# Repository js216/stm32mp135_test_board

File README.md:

# Test board using STM32MP135

A minimum working example of STM32MP135-based board, breaking out almost all the
pins.

### PCB layout

Find the KiCad files under `kicad/`. This includes the BOM and position files as
used to fabricate the board with JLCPCB. For quick reference, check out the
[`schematics.pdf`](https://github.com/js216/stm32mp135_test_board/blob/81400d63cfe211af686742da545c3347b2757c94/kicad/schematics.pdf).

### CubeMX files

The pin assignment was done using STM32CubeMX. Reluctantly, since it's one of
those bloated modern programs that manage to run slowly even on the fastest
computers available. But it does generate a nice overview of the pin assignment.

### Bare-metal projects

Under `baremetal` you can find a sequence of simple projects for getting started
with debugging this board. (See also the debugging walkthrough in
[this](https://embd.cc/linux-bringup-on-custom-stm32mp135-board) blog post.) The
projects are as follows:

- `blink` will blink the red LED on the board, thus proving that the chip works
  and that we have a way to program it (namely the `uart_boot.py` script,
  described in more details
  [here](https://embd.cc/boot-stm32mp135-over-uart-with-python)).

- `ddr_test`: Initialize DDR3L memory, fill it with pseudorandom bits, and
  confirm that reading from the memory returns the same bit sequence.

- `STM32DDRFW-UTIL`: A simplified version of the
  [tool](https://github.com/STMicroelectronics/STM32DDRFW-UTIL) provided by ST.

- `sd_test`: Initialize SD card, and read out the first few bytes.

- `usb_test`: Checks that data can be loaded from the USB interface (enumerated
  as a "flash drive") to the DDR memory.

- `qspi`: QUADSPI bring-up app.  Initialises the peripheral at ~1 MHz, then
  loops issuing JEDEC-ID reads (`0x9F` + 3 bytes) so the bus can be verified
  on a scope or logic analyser.  Designed for exercising QSPI wiring against
  a user-supplied FPGA slave.  The QUADSPI peripheral is poked via raw
  registers; HAL is used only for GPIO pin-mux, RCC clock muxing, and UART
  output.

All projects are completely independent of each other, and each directory
contains all drivers and other files needed to build the firmware image by just
calling `make`. This means that some of the source files are duplicated; so be
it! BSP packages are in my opinion too "integrated", where everything depends on
everything else. There are occasions---such as this one---where making a copy of
a couple files is the simplest and correct thing to do.

### Building a Linux system

The following directories contain the files needed to build a complete Linux
system image, ready for flashing to the board:

- `bootloader`: USB MSC Bootloader for STM32MP135
  [(link)](https://github.com/js216/stm32mp135-bootloader)
- `linux`: clone of the ST-modified kernel fork
  [(link)](https://github.com/STMicroelectronics/linux)
- `dtbs`: board-specific device tree sources

To build the project, run `make patch all` and watch the SD card image appear
under `build/`. More explanation can be found in
[this](https://embd.cc/build-linux-for-stm32mp135-in-under-50-lines-of-makefile)
blog post, or in the bootloader
[Readme](https://github.com/js216/stm32mp135-bootloader).

*Note:* The
["meta-Makefile"](https://github.com/js216/stm32mp135_test_board/blob/main/Makefile)
for this project is somewhat unusual: it does not track dependencies and its
recipes are fragile, so configuration changes may require editing the recipes
directly. Its purpose is not to provide a robust build system, but to serve as a
shortcut for repetitive command sequences. Being only about 50 lines, modifying
it directly is simpler than learning a separate configuration language. Treat it
as a minimal, linear workflow script wrapped in Make syntax rather than a
conventional build system.

### References

- [Ethernet on Bare-Metal STM32MP13](https://embd.cc/ethernet-on-baremetal-stm32mp135)
- [LCD/CTP on Bare-Metal STM32MP135](https://embd.cc/lcd-ctp-on-baremetal-stm32mp135)
- [Debugging STM32MP135 Kernel Decompression](https://embd.cc/debugging-stm32mp135-kernel-decompression)
- [Build Linux for STM32MP135 in under 50 Lines of Makefile](https://embd.cc/build-linux-for-stm32mp135-in-under-50-lines-of-makefile)
- [SD card on bare-metal STM32MP135](https://embd.cc/sdcard-on-bare-metal-stm32mp135)
- [Unsecuring STM32MP135 TrustZone](https://embd.cc/unsecuring-stm32mp135-trustzone)
- [Linux Bring-Up on a Custom STM32MP135 Board](https://embd.cc/linux-bringup-on-custom-stm32mp135-board)
- [USB Bring-Up on a Custom STM32MP135 Board](https://embd.cc/usb-bringup-on-custom-stm32mp135-board)
- [STM32MP135 Flashing via USB with STM32CubeProg](https://embd.cc/stm32mp135-linux-cubeprog)
- [Boot STM32MP135 Over UART With Python](https://embd.cc/boot-stm32mp135-over-uart-with-python)
- [Buildroot files for a similar project](https://github.com/js216/stm32mp135_simple/tree/main)

### Author

Jakob Kastelic, Stanford Research Systems

NOTE: PORTIONS OF THIS REPOSITORY CONTAIN SOURCE CODE COPYRIGHTED BY
STMICROELECTRONICS. SUCH FILES ARE PROVIDED UNDER STMICROELECTRONICS' ORIGINAL
LICENSE TERMS, WHICH ARE INCLUDED WITH THOSE FILES. NO RIGHTS ARE GRANTED BEYOND
THOSE TERMS. THIS REPOSITORY MAY NOT BE USED WITH NON-ST HARDWARE UNLESS
PERMITTED BY ST'S LICENSE. ALL PROPRIETARY NOTICES MUST REMAIN INTACT.

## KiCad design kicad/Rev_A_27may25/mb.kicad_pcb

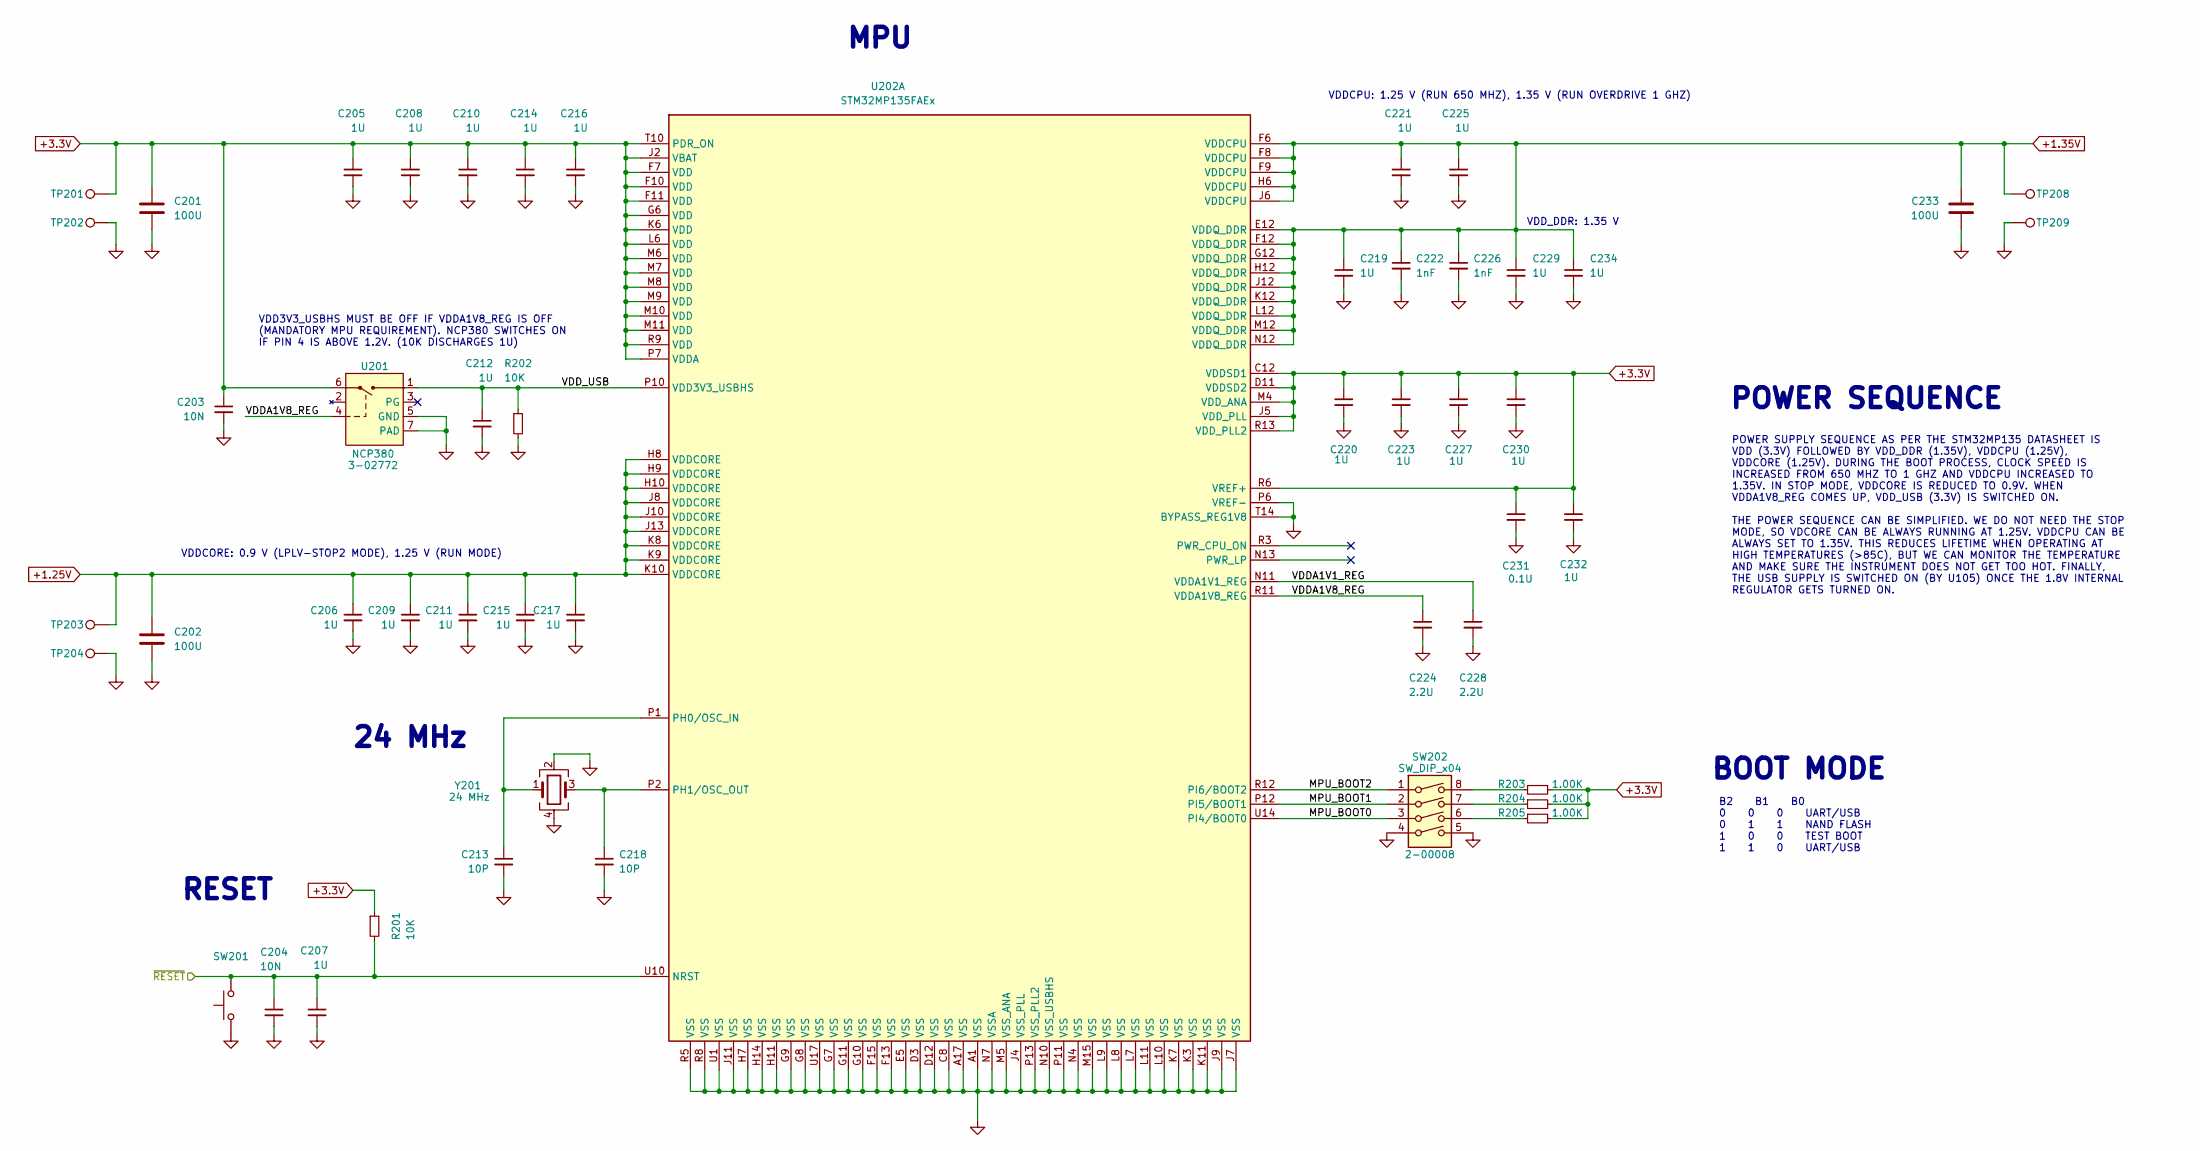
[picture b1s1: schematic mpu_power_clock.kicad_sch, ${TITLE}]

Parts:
C201, C202, C233: 100U; C_1206_3216Metric; JLCPCB C15008
C203, C204: 10N; C_0402_1005Metric; JLCPCB C15195
C205, C206, C207, C208, C209, C210, C211, C212, C214, C215, C216, C217, C219, C220, C221, C223, C225, C227, C229, C230, C232, C234: 1U; C_0402_1005Metric; JLCPCB C52923
C213, C218: 10P; C_0402_1005Metric; JLCPCB C32949
C222, C226: 1nF; C_0402_1005Metric; JLCPCB C1523
C224, C228: 2.2U; C_0402_1005Metric; JLCPCB C12530
C231: 0.1U; C_0402_1005Metric; JLCPCB C307331
R201, R202: 10K; R_0402_1005Metric; JLCPCB C25744
R203, R204, R205: 1.00K; R_0402_1005Metric; JLCPCB C11702
SW201: Omron B3F-1052; SW_TH_Tactile_Omron_B3F-10xx
SW202: SW_DIP_x04; SW_DIP_SPSTx04_Slide_9.78x12.34mm_W7.62mm_P2.54mm
TP201, TP203, TP208: Keystone 5005 (red); TestPoint_Keystone_5005-5009_Compact
TP202, TP204, TP209: Keystone 5006 (black); TestPoint_Keystone_5005-5009_Compact
U201: NCP380; DFN-6-1EP_2x2mm_P0.65mm_EP1x1.6mm; JLCPCB C145185
U202: STM32MP135FAEx; LFBGA-289_14x14mm_Layout17x17_P0.8mm; JLCPCB C7501745
Y201: 24 MHz; Crystal_SMD_3225-4Pin_3.2x2.5mm; MPN YXC Crystal Oscillators X322524MRB4SI; JLCPCB C70571

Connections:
+1.25V: C202.1, C206.1, C209.1, C211.1, C215.1, C217.1, TP203.1, U202.H8 (VDDCORE), U202.H9 (VDDCORE), U202.H10 (VDDCORE), U202.J8 (VDDCORE), U202.J10 (VDDCORE), U202.J13 (VDDCORE), U202.K8 (VDDCORE), U202.K9 (VDDCORE), U202.K10 (VDDCORE)
+1.35V: C219.1, C221.1, C222.1, C225.1, C226.1, C229.1, C233.1, C234.1, TP208.1, U202.E12 (VDDQ_DDR), U202.F6 (VDDCPU), U202.F8 (VDDCPU), U202.F9 (VDDCPU), U202.F12 (VDDQ_DDR), U202.G12 (VDDQ_DDR), U202.H6 (VDDCPU), U202.H12 (VDDQ_DDR), U202.J6 (VDDCPU), U202.J12 (VDDQ_DDR), U202.K12 (VDDQ_DDR), U202.L12 (VDDQ_DDR), U202.M12 (VDDQ_DDR), U202.N12 (VDDQ_DDR); also elsewhere on the board
+3.3V: C201.1, C203.1, C205.1, C208.1, C210.1, C214.1, C216.1, C220.1, C223.1, C227.1, C230.1, C231.1, C232.1, R201.1, R203.2, R204.2, R205.2, TP201.1, U201.6, U202.C12 (VDDSD1), U202.D11 (VDDSD2), U202.F7 (VDD), U202.F10 (VDD), U202.F11 (VDD), U202.G6 (VDD), U202.J2 (VBAT), U202.J5 (VDD_PLL), U202.K6 (VDD), U202.L6 (VDD), U202.M4 (VDD_ANA), U202.M6 (VDD), U202.M7 (VDD), U202.M8 (VDD), U202.M9 (VDD), U202.M10 (VDD), U202.M11 (VDD), U202.P7 (VDDA), U202.R6 (VREF+), U202.R9 (VDD), U202.R13 (VDD_PLL2), U202.T10 (PDR_ON); also elsewhere on the board
/MPU Power & Clock/MPU_BOOT0: SW202.3, U202.U14 (PI4/BOOT0)
/MPU Power & Clock/MPU_BOOT1: SW202.2, U202.P12 (PI5/BOOT1)
/MPU Power & Clock/MPU_BOOT2: SW202.1, U202.R12 (PI6/BOOT2)
/MPU Power & Clock/VDDA1V1_REG: C228.1, U202.N11 (VDDA1V1_REG)
/MPU Power & Clock/VDDA1V8_REG: C224.1, U201.4, U202.R11 (VDDA1V8_REG)
/MPU Power & Clock/VDD_USB: C212.1, R202.1, U201.1, U202.P10 (VDD3V3_USBHS)
/~RESET: C204.1, C207.1, R201.2, SW201.2, U202.U10 (NRST); also elsewhere on the board
GND: C201.2, C202.2, C203.2, C204.2, C205.2, C206.2, C207.2, C208.2, C209.2, C210.2, C211.2, C212.2, C213.2, C214.2, C215.2, C216.2, C217.2, C218.2, C219.2, C220.2, C221.2, C222.2, C223.2, C224.2, C225.2, C226.2, C227.2, C228.2, C229.2, C230.2, C231.2, C232.2, C233.2, C234.2, R202.2, SW201.1, SW202.4, SW202.5, TP202.1, TP204.1, TP209.1, U201.5 (GND), U201.7 (PAD), U202.A1 (VSS), U202.A17 (VSS), U202.C8 (VSS), U202.D3 (VSS), U202.D12 (VSS), U202.E5 (VSS), U202.F13 (VSS), U202.F15 (VSS), U202.G7 (VSS), U202.G8 (VSS), U202.G9 (VSS), U202.G10 (VSS), U202.G11 (VSS), U202.H7 (VSS), U202.H11 (VSS), U202.H14 (VSS), U202.J4 (VSS_PLL), U202.J7 (VSS), U202.J9 (VSS), U202.J11 (VSS), U202.K3 (VSS), U202.K7 (VSS), U202.K11 (VSS), U202.L7 (VSS), U202.L8 (VSS), U202.L9 (VSS), U202.L10 (VSS), U202.L11 (VSS), U202.M5 (VSS_ANA), U202.M15 (VSS), U202.N4 (VSS), U202.N7 (VSSA), U202.N10 (VSS_USBHS), U202.P6 (VREF-), U202.P11 (VSS), U202.P13 (VSS_PLL2), U202.R5 (VSS), U202.R8 (VSS), U202.T14 (BYPASS_REG1V8), U202.U1 (VSS), U202.U17 (VSS), Y201.2, Y201.4; also elsewhere on the board
unnamed: R203.1, SW202.8
unnamed: R204.1, SW202.7
unnamed: R205.1, SW202.6
unnamed: C213.1, U202.P1 (PH0/OSC_IN), Y201.1
unnamed: C218.1, U202.P2 (PH1/OSC_OUT), Y201.3

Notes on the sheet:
B2 B1 B0 0 0 0 UART/USB 0 1 1 NAND FLASH 1 0 0 TEST BOOT 1 1 0 UART/USB
VDDCPU: 1.25 V (RUN 650 MHZ), 1.35 V (RUN OVERDRIVE 1 GHZ)
MPU
BOOT MODE
POWER SUPPLY SEQUENCE AS PER THE STM32MP135 DATASHEET IS VDD (3.3V) FOLLOWED BY VDD_DDR (1.35V), VDDCPU (1.25V), VDDCORE (1.25V). DURING THE BOOT PROCESS, CLOCK SPEED IS INCREASED FROM 650 MHZ TO 1 GHZ AND VDDCPU INCREASED TO 1.35V. IN STOP MODE, VDDCORE IS REDUCED TO 0.9V. WHEN VDDA1V8_REG COMES U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
POWER SEQUENCE
VDD3V3_USBHS MUST BE OFF IF VDDA1V8_REG IS OFF (MANDATORY MPU REQUIREMENT). NCP380 SWITCHES ON IF PIN 4 IS ABOVE 1.2V. (10K DISCHARGES 1U)
VDD_DDR: 1.35 V
24 MHz
VDDCORE: 0.9 V (LPLV-STOP2 MODE), 1.25 V (RUN MODE)
RESET

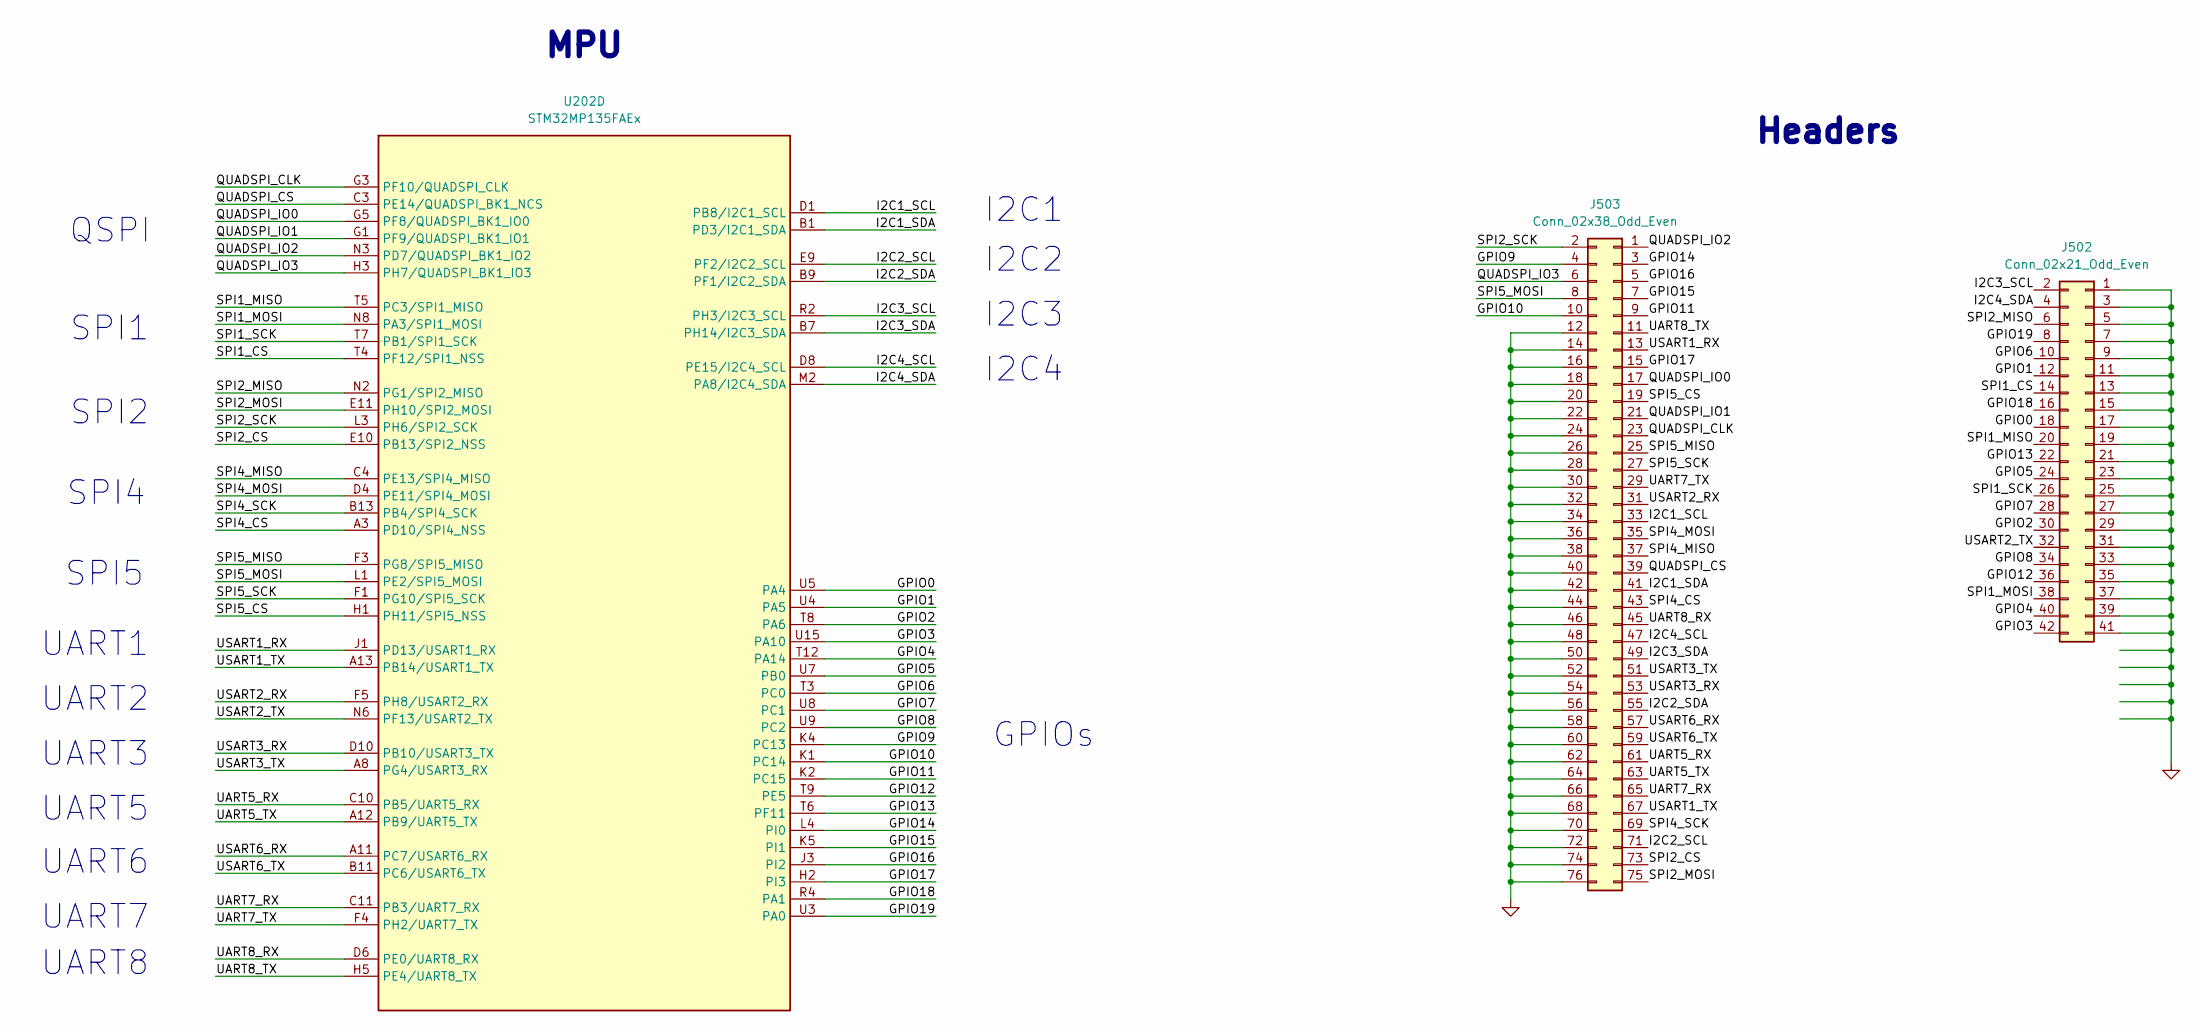
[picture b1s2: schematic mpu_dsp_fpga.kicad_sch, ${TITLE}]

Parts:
J502: Conn_02x21_Odd_Even; PinHeader_2x21_P2.54mm_Vertical
J503: Conn_02x38_Odd_Even; PinHeader_2x38_P2.54mm_Vertical
U202: STM32MP135FAEx; LFBGA-289_14x14mm_Layout17x17_P0.8mm; JLCPCB C7501745

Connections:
/MPU Extra Pins/GPIO0: J502.18, U202.U5 (PA4)
/MPU Extra Pins/GPIO1: J502.12, U202.U4 (PA5)
/MPU Extra Pins/GPIO2: J502.30, U202.T8 (PA6)
/MPU Extra Pins/GPIO3: J502.42, U202.U15 (PA10)
/MPU Extra Pins/GPIO4: J502.40, U202.T12 (PA14)
/MPU Extra Pins/GPIO5: J502.24, U202.U7 (PB0)
/MPU Extra Pins/GPIO6: J502.10, U202.T3 (PC0)
/MPU Extra Pins/GPIO7: J502.28, U202.U8 (PC1)
/MPU Extra Pins/GPIO8: J502.34, U202.U9 (PC2)
/MPU Extra Pins/GPIO9: J503.4, U202.K4 (PC13)
/MPU Extra Pins/GPIO10: J503.10, U202.K1 (PC14)
/MPU Extra Pins/GPIO11: J503.9, U202.K2 (PC15)
/MPU Extra Pins/GPIO12: J502.36, U202.T9 (PE5)
/MPU Extra Pins/GPIO13: J502.22, U202.T6 (PF11)
/MPU Extra Pins/GPIO14: J503.3, U202.L4 (PI0)
/MPU Extra Pins/GPIO15: J503.7, U202.K5 (PI1)
/MPU Extra Pins/GPIO16: J503.5, U202.J3 (PI2)
/MPU Extra Pins/GPIO17: J503.15, U202.H2 (PI3)
/MPU Extra Pins/GPIO18: J502.16, U202.R4 (PA1)
/MPU Extra Pins/GPIO19: J502.8, U202.U3 (PA0)
/MPU Extra Pins/I2C1_SCL: J503.33, U202.D1 (PB8/I2C1_SCL)
/MPU Extra Pins/I2C1_SDA: J503.41, U202.B1 (PD3/I2C1_SDA)
/MPU Extra Pins/I2C2_SCL: J503.71, U202.E9 (PF2/I2C2_SCL)
/MPU Extra Pins/I2C2_SDA: J503.55, U202.B9 (PF1/I2C2_SDA)
/MPU Extra Pins/I2C3_SCL: J502.2, U202.R2 (PH3/I2C3_SCL)
/MPU Extra Pins/I2C3_SDA: J503.49, U202.B7 (PH14/I2C3_SDA)
/MPU Extra Pins/I2C4_SCL: J503.47, U202.D8 (PE15/I2C4_SCL)
/MPU Extra Pins/I2C4_SDA: J502.4, U202.M2 (PA8/I2C4_SDA)
/MPU Extra Pins/QUADSPI_CLK: J503.23, U202.G3 (PF10/QUADSPI_CLK)
/MPU Extra Pins/QUADSPI_CS: J503.39, U202.C3 (PE14/QUADSPI_BK1_NCS)
/MPU Extra Pins/QUADSPI_IO0: J503.17, U202.G5 (PF8/QUADSPI_BK1_IO0)
/MPU Extra Pins/QUADSPI_IO1: J503.21, U202.G1 (PF9/QUADSPI_BK1_IO1)
/MPU Extra Pins/QUADSPI_IO2: J503.1, U202.N3 (PD7/QUADSPI_BK1_IO2)
/MPU Extra Pins/QUADSPI_IO3: J503.6, U202.H3 (PH7/QUADSPI_BK1_IO3)
/MPU Extra Pins/SPI1_CS: J502.14, U202.T4 (PF12/SPI1_NSS)
/MPU Extra Pins/SPI1_MISO: J502.20, U202.T5 (PC3/SPI1_MISO)
/MPU Extra Pins/SPI1_MOSI: J502.38, U202.N8 (PA3/SPI1_MOSI)
/MPU Extra Pins/SPI1_SCK: J502.26, U202.T7 (PB1/SPI1_SCK)
/MPU Extra Pins/SPI2_CS: J503.73, U202.E10 (PB13/SPI2_NSS)
/MPU Extra Pins/SPI2_MISO: J502.6, U202.N2 (PG1/SPI2_MISO)
/MPU Extra Pins/SPI2_MOSI: J503.75, U202.E11 (PH10/SPI2_MOSI)
/MPU Extra Pins/SPI2_SCK: J503.2, U202.L3 (PH6/SPI2_SCK)
/MPU Extra Pins/SPI4_CS: J503.43, U202.A3 (PD10/SPI4_NSS)
/MPU Extra Pins/SPI4_MISO: J503.37, U202.C4 (PE13/SPI4_MISO)
/MPU Extra Pins/SPI4_MOSI: J503.35, U202.D4 (PE11/SPI4_MOSI)
/MPU Extra Pins/SPI4_SCK: J503.69, U202.B13 (PB4/SPI4_SCK)
/MPU Extra Pins/SPI5_CS: J503.19, U202.H1 (PH11/SPI5_NSS)
/MPU Extra Pins/SPI5_MISO: J503.25, U202.F3 (PG8/SPI5_MISO)
/MPU Extra Pins/SPI5_MOSI: J503.8, U202.L1 (PE2/SPI5_MOSI)
/MPU Extra Pins/SPI5_SCK: J503.27, U202.F1 (PG10/SPI5_SCK)
/MPU Extra Pins/UART5_RX: J503.61, U202.C10 (PB5/UART5_RX)
/MPU Extra Pins/UART5_TX: J503.63, U202.A12 (PB9/UART5_TX)
/MPU Extra Pins/UART7_RX: J503.65, U202.C11 (PB3/UART7_RX)
/MPU Extra Pins/UART7_TX: J503.29, U202.F4 (PH2/UART7_TX)
/MPU Extra Pins/UART8_RX: J503.45, U202.D6 (PE0/UART8_RX)
/MPU Extra Pins/UART8_TX: J503.11, U202.H5 (PE4/UART8_TX)
/MPU Extra Pins/USART1_RX: J503.13, U202.J1 (PD13/USART1_RX)
/MPU Extra Pins/USART1_TX: J503.67, U202.A13 (PB14/USART1_TX)
/MPU Extra Pins/USART2_RX: J503.31, U202.F5 (PH8/USART2_RX)
/MPU Extra Pins/USART2_TX: J502.32, U202.N6 (PF13/USART2_TX)
/MPU Extra Pins/USART3_RX: J503.53, U202.D10 (PB10/USART3_TX)
/MPU Extra Pins/USART3_TX: J503.51, U202.A8 (PG4/USART3_RX)
/MPU Extra Pins/USART6_RX: J503.57, U202.A11 (PC7/USART6_RX)
/MPU Extra Pins/USART6_TX: J503.59, U202.B11 (PC6/USART6_TX)
GND: J502.1, J502.3, J502.5, J502.7, J502.9, J502.11, J502.13, J502.15, J502.17, J502.19, J502.21, J502.23, J502.25, J502.27, J502.29, J502.31, J502.33, J502.35, J502.37, J502.39, J502.41, J503.12, J503.14, J503.16, J503.18, J503.20, J503.22, J503.24, J503.26, J503.28, J503.30, J503.32, J503.34, J503.36, J503.38, J503.40, J503.42, J503.44, J503.46, J503.48, J503.50, J503.52, J503.54, J503.56, J503.58, J503.60, J503.62, J503.64, J503.66, J503.68, J503.70, J503.72, J503.74, J503.76; also elsewhere on the board

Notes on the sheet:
I2C1
UART6
Headers
UART3
I2C3
SPI5
UART1
UART5
UART2
SPI1
GPIOs
SPI2
I2C2
QSPI
UART8
MPU
SPI4
I2C4
UART7

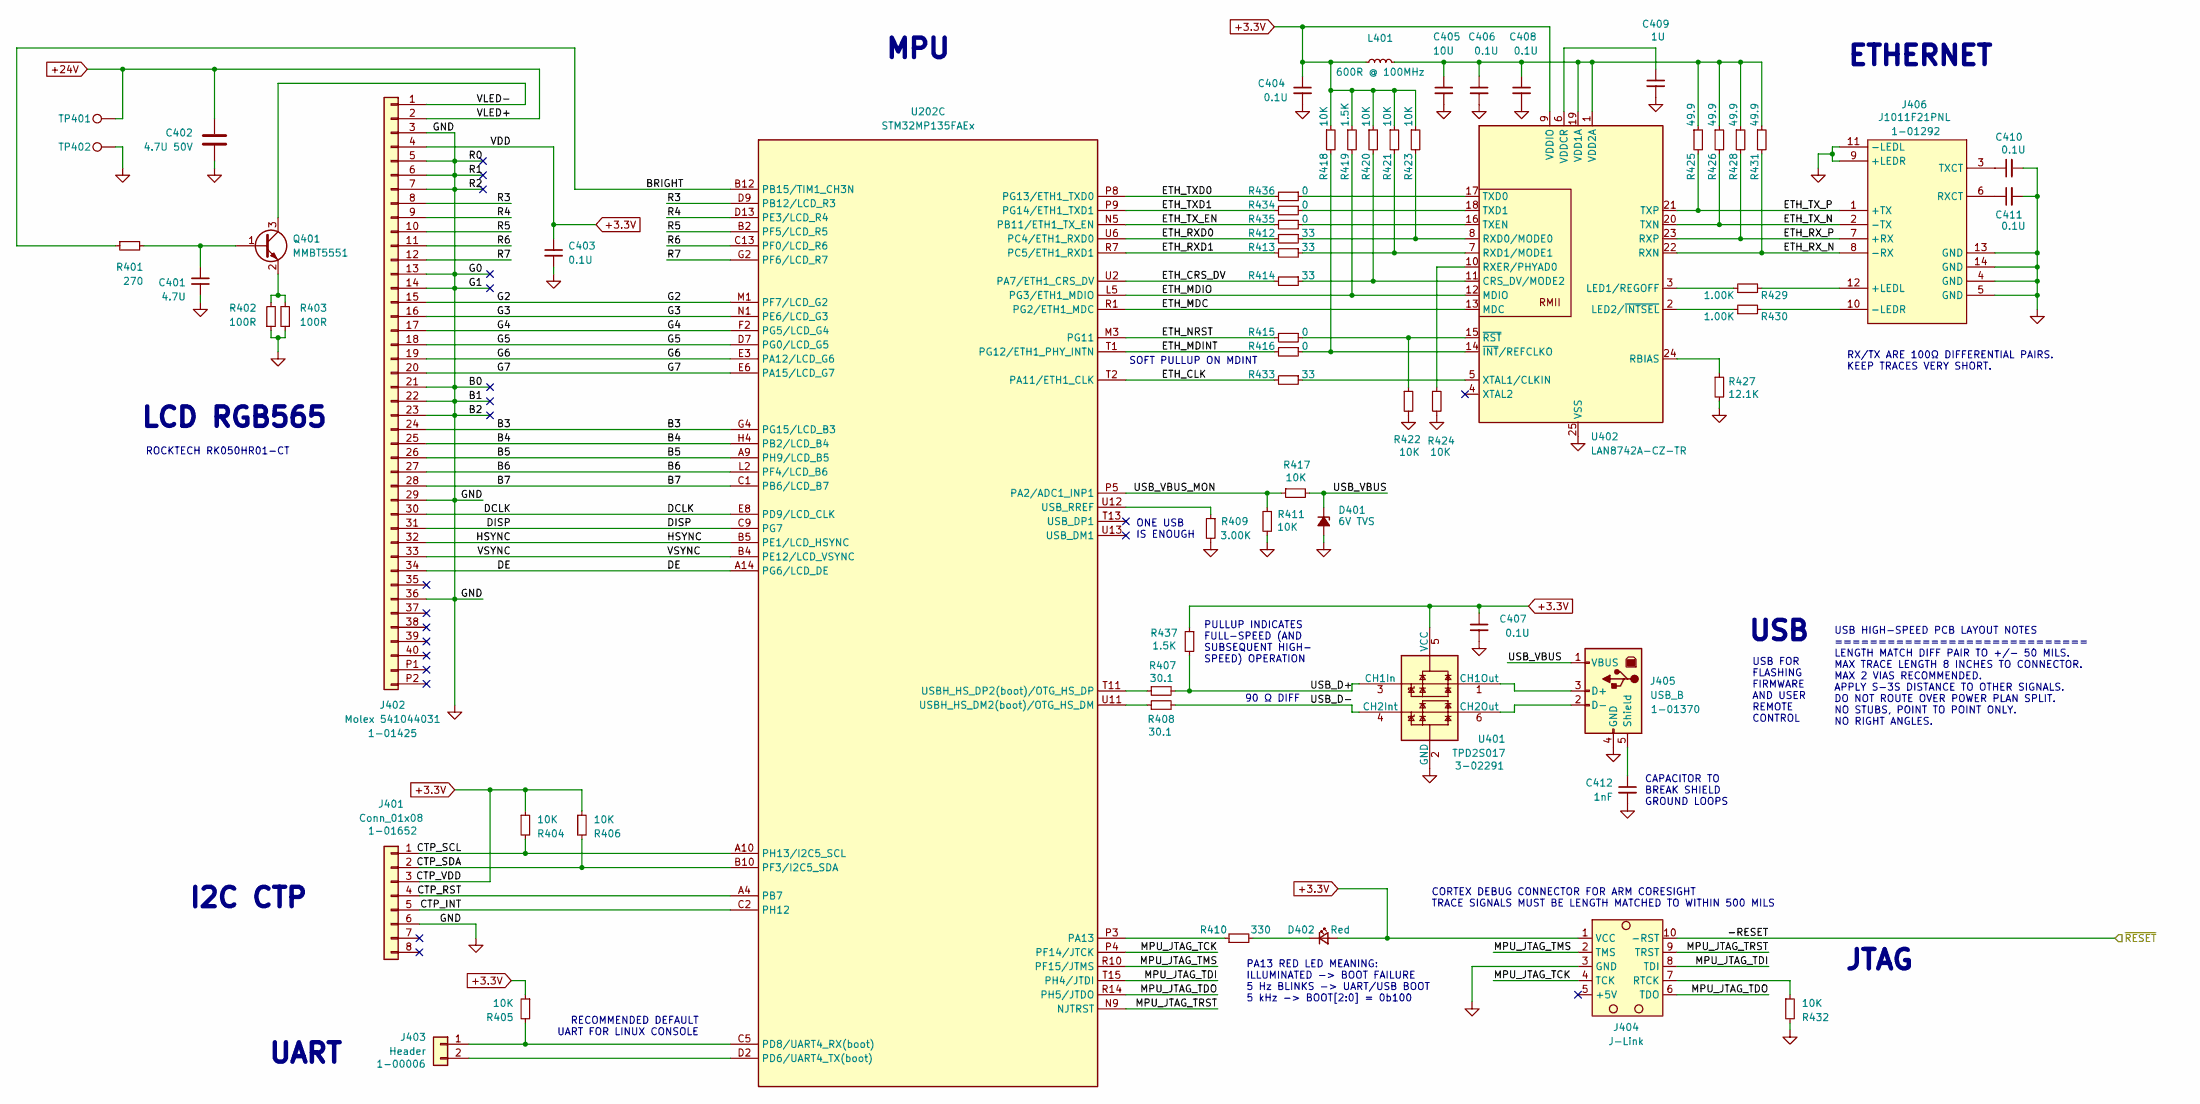
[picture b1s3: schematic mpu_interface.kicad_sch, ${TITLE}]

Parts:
C401: 4.7U; C_0402_1005Metric; JLCPCB C23733
C402: 4.7U 50V; C_1206_3216Metric; JLCPCB C29823
C403, C404, C406, C407, C408, C410, C411: 0.1U; C_0402_1005Metric; JLCPCB C307331
C405: 10U; C_0402_1005Metric; JLCPCB C15525
C409: 1U; C_0402_1005Metric; JLCPCB C52923
C412: 1nF; C_0402_1005Metric; JLCPCB C1523
D401: 6V TVS; SOD882T; MPN ESDAXLC6-1BT2Y; JLCPCB C472589
D402: Red; LED_0603_1608Metric; JLCPCB C2286
J401: Conn_01x08; CONN6x1_FH34SRJ-6S-0.5SH50_HIR; MPN FH34SRJ-6S-0.5SH(50); JLCPCB C5213748
J402: Molex 541044031; CON_541044031_MOL; JLCPCB C164172
J403: Header; PinHeader_1x02_P2.54mm_Vertical
J404: J-Link
J405: USB_B; USBR-B-S-S-O-TH
J406: J1011F21PNL
L401: 600R @ 100MHz; L_0603_1608Metric; JLCPCB C1002
Q401: MMBT5551; SOT-23; JLCPCB C2145
R401: 270; R_0603_1608Metric; JLCPCB C22966
R402, R403: 100R; R_0402_1005Metric; JLCPCB C25076
R404, R405, R406, R411, R417, R418, R420, R421, R422, R423, R424, R432: 10K; R_0402_1005Metric; JLCPCB C25744
R407, R408: 30.1; R_0402_1005Metric; JLCPCB C67234
R409: 3.00K; R_0603_1608Metric; JLCPCB C4211
R410: 330; R_0402_1005Metric; JLCPCB C25104
R412, R413, R414, R433: 33; R_0402_1005Metric; JLCPCB C25105
R415, R416, R434, R435, R436: 0; R_0402_1005Metric; JLCPCB C17168
R419, R437: 1.5K; R_0402_1005Metric; JLCPCB C25867
R425, R426, R428, R431: 49.9; R_0402_1005Metric; JLCPCB C25120
R427: 12.1K; R_0402_1005Metric; JLCPCB C25852
R429, R430: 1.00K; R_0402_1005Metric; JLCPCB C11702
TP401: Keystone 5005 (red); TestPoint_Keystone_5005-5009_Compact
TP402: Keystone 5006 (black); TestPoint_Keystone_5005-5009_Compact
U202: STM32MP135FAEx; LFBGA-289_14x14mm_Layout17x17_P0.8mm; JLCPCB C7501745
U401: TPD2S017; SOT-23-6; JLCPCB C880115
U402: LAN8742A-CZ-TR; VQFN-24-1EP_4x4mm_P0.5mm_EP2.5x2.5mm_ThermalVias; JLCPCB C621424

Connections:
+3.3V: C403.1, C404.1, C407.1, D402.2 (A), J401.3, J402.4, J404.1 (VCC), L401.1, R404.1, R405.1, R406.1, R418.1, R419.1, R420.1, R421.1, R423.1, R437.1, U401.5 (VCC), U402.9 (VDDIO); also elsewhere on the board
+24V: C402.1, J402.2, TP401.1
/MPU Interface/B3: J402.24, U202.G4 (PG15/LCD_B3)
/MPU Interface/B4: J402.25, U202.H4 (PB2/LCD_B4)
/MPU Interface/B5: J402.26, U202.A9 (PH9/LCD_B5)
/MPU Interface/B6: J402.27, U202.L2 (PF4/LCD_B6)
/MPU Interface/B7: J402.28, U202.C1 (PB6/LCD_B7)
/MPU Interface/BRIGHT: R401.1, U202.B12 (PB15/TIM1_CH3N)
/MPU Interface/CTP_INT: J401.5, U202.C2 (PH12)
/MPU Interface/CTP_RST: J401.4, U202.A4 (PB7)
/MPU Interface/CTP_SCL: J401.1, R404.2, U202.A10 (PH13/I2C5_SCL)
/MPU Interface/CTP_SDA: J401.2, R406.2, U202.B10 (PF3/I2C5_SDA)
/MPU Interface/DCLK: J402.30, U202.E8 (PD9/LCD_CLK)
/MPU Interface/DE: J402.34, U202.A14 (PG6/LCD_DE)
/MPU Interface/DISP: J402.31, U202.C9 (PG7)
/MPU Interface/ETH_CLK: R433.2, U202.T2 (PA11/ETH1_CLK)
/MPU Interface/ETH_CRS_DV: R414.2, U202.U2 (PA7/ETH1_CRS_DV)
/MPU Interface/ETH_MDC: U202.R1 (PG2/ETH1_MDC), U402.13 (MDC)
/MPU Interface/ETH_MDINT: R416.2, U202.T1 (PG12/ETH1_PHY_INTN)
/MPU Interface/ETH_MDIO: R419.2, U202.L5 (PG3/ETH1_MDIO), U402.12 (MDIO)
/MPU Interface/ETH_NRST: R415.2, U202.M3 (PG11)
/MPU Interface/ETH_RXD0: R412.2, U202.U6 (PC4/ETH1_RXD0)
/MPU Interface/ETH_RXD1: R413.2, U202.R7 (PC5/ETH1_RXD1)
/MPU Interface/ETH_RX_N: J406.8 (-RX), R431.2, U402.22 (RXN)
/MPU Interface/ETH_RX_P: J406.7 (+RX), R428.2, U402.23 (RXP)
/MPU Interface/ETH_TXD0: R436.2, U202.P8 (PG13/ETH1_TXD0)
/MPU Interface/ETH_TXD1: R434.2, U202.P9 (PG14/ETH1_TXD1)
/MPU Interface/ETH_TX_EN: R435.2, U202.N5 (PB11/ETH1_TX_EN)
/MPU Interface/ETH_TX_N: J406.2 (-TX), R426.2, U402.20 (TXN)
/MPU Interface/ETH_TX_P: J406.1 (+TX), R425.2, U402.21 (TXP)
/MPU Interface/G2: J402.15, U202.M1 (PF7/LCD_G2)
/MPU Interface/G3: J402.16, U202.N1 (PE6/LCD_G3)
/MPU Interface/G4: J402.17, U202.F2 (PG5/LCD_G4)
/MPU Interface/G5: J402.18, U202.D7 (PG0/LCD_G5)
/MPU Interface/G6: J402.19, U202.E3 (PA12/LCD_G6)
/MPU Interface/G7: J402.20, U202.E6 (PA15/LCD_G7)
/MPU Interface/HSYNC: J402.32, U202.B5 (PE1/LCD_HSYNC)
/MPU Interface/MPU_JTAG_TCK: J404.4 (TCK), U202.P4 (PF14/JTCK)
/MPU Interface/MPU_JTAG_TDI: J404.8 (TDI), U202.T15 (PH4/JTDI)
/MPU Interface/MPU_JTAG_TDO: J404.6 (TDO), U202.R14 (PH5/JTDO)
/MPU Interface/MPU_JTAG_TMS: J404.2 (TMS), U202.R10 (PF15/JTMS)
/MPU Interface/MPU_JTAG_TRST: J404.9 (TRST), U202.N9 (NJTRST)
/MPU Interface/R3: J402.8, U202.D9 (PB12/LCD_R3)
/MPU Interface/R4: J402.9, U202.D13 (PE3/LCD_R4)
/MPU Interface/R5: J402.10, U202.B2 (PF5/LCD_R5)
/MPU Interface/R6: J402.11, U202.C13 (PF0/LCD_R6)
/MPU Interface/R7: J402.12, U202.G2 (PF6/LCD_R7)
/MPU Interface/USB_D+: R407.2, R437.2, U401.3 (CH1In)
/MPU Interface/USB_D-: R408.2, U401.4 (CH2Int)
/MPU Interface/USB_VBUS: D401.1 (K), J405.1 (VBUS), R417.2
/MPU Interface/USB_VBUS_MON: R411.1, R417.1, U202.P5 (PA2/ADC1_INP1)
/MPU Interface/VLED-: J402.1, Q401.3 (C)
/MPU Interface/VSYNC: J402.33, U202.B4 (PE12/LCD_VSYNC)
/~RESET: J404.10 (-RST); also elsewhere on the board
GND: C401.2, C402.2, C403.2, C404.2, C405.2, C406.2, C407.2, C408.2, C409.2, C410.2, C411.2, C412.2, D401.2 (A), J401.6, J402.3, J402.5, J402.6, J402.7, J402.13, J402.14, J402.21, J402.22, J402.23, J402.29, J402.36, J404.3 (GND), J405.4 (GND), J406.4 (GND), J406.5 (GND), J406.9 (+LEDR), J406.11 (-LEDL), J406.13 (GND), J406.14 (GND), R402.1, R403.1, R409.2, R411.2, R422.2, R424.2, R427.2, R432.2, TP402.1, U401.2 (GND), U402.25 (VSS); also elsewhere on the board
unnamed: D402.1 (K), R410.2
unnamed: J403.1, R405.2, U202.C5 (PD8/UART4_RX(boot))
unnamed: J403.2, U202.D2 (PD6/UART4_TX(boot))
unnamed: J404.7 (RTCK), R432.1
unnamed: J405.3 (D+), U401.1 (CH1Out)
unnamed: J405.2 (D-), U401.6 (CH2Out)
unnamed: C412.1, J405.5 (Shield)
unnamed: J406.12 (+LEDL), R429.2
unnamed: J406.10 (-LEDR), R430.2
unnamed: C411.1, J406.6 (RXCT)
unnamed: C410.1, J406.3 (TXCT)
unnamed: C401.1, Q401.1 (B), R401.2
unnamed: Q401.2 (E), R402.2, R403.2
unnamed: R410.1, U202.P3 (PA13)
unnamed: R408.1, U202.U11 (USBH_HS_DM2(boot)/OTG_HS_DM)
unnamed: R407.1, U202.T11 (USBH_HS_DP2(boot)/OTG_HS_DP)
unnamed: R409.1, U202.U12 (USB_RREF)
unnamed: R414.1, R420.2, U402.11 (CRS_DV/MODE2)
unnamed: R429.1, U402.3 (LED1/REGOFF)
unnamed: R430.1, U402.2 (LED2/~INTSEL)
unnamed: R427.1, U402.24 (RBIAS)
unnamed: R412.1, R423.2, U402.8 (RXD0/MODE0)
unnamed: R413.1, R421.2, U402.7 (RXD1/MODE1)
unnamed: R424.1, U402.10 (RXER/PHYAD0)
unnamed: R436.1, U402.17 (TXD0)
unnamed: R434.1, U402.18 (TXD1)
unnamed: R435.1, U402.16 (TXEN)
unnamed: C405.1, C406.1, C408.1, L401.2, R425.1, R426.1, R428.1, R431.1, U402.1 (VDD2A), U402.19 (VDD1A)
unnamed: C409.1, U402.6 (VDDCR)
unnamed: R433.1, U402.5 (XTAL1/CLKIN)
unnamed: R416.1, R418.2, U402.14 (~INT/REFCLKO)
unnamed: R415.1, R422.1, U402.15 (~RST)

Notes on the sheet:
USB
CAPACITOR TO BREAK SHIELD GROUND LOOPS
SOFT PULLUP ON MDINT
ETHERNET
ONE USB IS ENOUGH
MPU
I2C CTP
LCD RGB565
RX/TX ARE 100Ω DIFFERENTIAL PAIRS. KEEP TRACES VERY SHORT.
PA13 RED LED MEANING: ILLUMINATED -> BOOT FAILURE 5 Hz BLINKS -> UART/USB BOOT 5 kHz -> BOOT[2:0] = 0b100
RECOMMENDED DEFAULT UART FOR LINUX CONSOLE
JTAG
CORTEX DEBUG CONNECTOR FOR ARM CORESIGHT TRACE SIGNALS MUST BE LENGTH MATCHED TO WITHIN 500 MILS
UART
USB HIGH-SPEED PCB LAYOUT NOTES ============================= LENGTH MATCH DIFF PAIR TO +/- 50 MILS. MAX TRACE LENGTH 8 INCHES TO CONNECTOR. MAX 2 VIAS RECOMMENDED. APPLY S-3S DISTANCE TO OTHER SIGNALS. DO NOT ROUTE OVER POWER PLAN SPLIT. NO STUBS, POINT TO POINT ONLY. NO RIGHT ANGLES.
PULLUP INDICATES FULL-SPEED (AND SUBSEQUENT HIGH- SPEED) OPERATION
USB FOR FLASHING FIRMWARE AND USER REMOTE CONTROL
90 Ω DIFF
ROCKTECH RK050HR01-CT

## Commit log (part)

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2025-11-19 board as built
2025-11-19 add pcb photo
2025-11-22 add ddr_test (work in progress)
2025-11-24 add ddr util
2025-11-24 simplify
2025-11-26 sd test initial commit
2025-12-01 write SD to DRAM correctly
2025-12-02 add usb_test
2025-12-03 take exceptions to arm mode
    Previously, the Reset_Handler took all exceptions to Thumb mode:
    ORR R0, R0, #(0x1 << 30)
    Now, we take them to Arm mode:
    BIC R0, R0, #(1 << 30)
    With that, HAL_PCD_IRQHandler is called without locking up the system.
2025-12-03 minor cleanup
2025-12-03 integrate msc, but it doesn't work yet
2025-12-03 define callbacks
2025-12-03 remove prints from HAL_PCD_IRQHandler
2025-12-03 fix misaligned data access in USB driver
2025-12-04 make more space and change Os to O1
2025-12-05 optimize reads, remove etzpc
2025-12-05 clang-format
2025-12-05 cleanup makefile and load script
2025-12-06 linting
2025-12-06 more linting
2026-04-27 add baremetal/qspi: standalone QUADSPI bring-up app
    Self-contained bare-metal demo modeled on baremetal/blink: HAL_Init +
    SystemClock_Config + UART4 setup, then qspi_init at ~1 MHz and a JEDEC-ID
    read loop printing once per second over UART4. Per-board pinout in
    src/board.h (SR835-MB default; -DEVB switches to STM32MP135F-DK CN8).
    The QUADSPI peripheral is driven through raw register writes; HAL is used
    only for GPIO pin-mux, RCC clock muxing, and UART -- a strict subset of
2026-04-28 baremetal/qspi: full QSPI flash test shell + automated bench tests
    Replaces the earlier one-shot JEDEC-ID demo with a complete UART CLI
    exercising every command Linux's m25p80 NOR-flash driver issues. The
    project is derived from the bootloader (cold-boot DFU path: clocks,
    STPMIC1 VDDCORE bump, ETZPC unsecure, GPIO unsecure, UART4) and runs
    from SYSRAM.
    CLI commands (single character + args, \r-terminated):
2026-04-28 baremetal/qspi: strict flash conformance suite (29 blocks, 50 bullets)
    Tightens the QSPI test suite from "host-emitted-right-command" semantics
    to end-to-end Linux-bootability semantics: the slave must round-trip
    program / erase / read; honour WIP and WEL bits; expose JEDEC ID + SFDP
    that the m25p80 driver can probe; respect QE for quad ops; preserve page
    boundaries on PP; clear WEL on soft reset; ignore programs without WREN;
    go silent under DPD. In addition the FPGA's per-frame UART (op=hh
2026-04-28 gitignore: ignore __pycache__
    Test artefact directories from the baremetal/qspi/ verify.py invocation
    land here when the test framework imports the module.
2026-04-28 baremetal/qspi: 1 MB throughput sweep across 5 SCLK steps
    New Block 2 inserted right after JEDEC plausibility. Bumps prescaler
    in 5 steps (203, 63, 15, 5, 2 -> SCLK 1.31 / 4.16 / 16.6 / 44.4 /
    88.7 MHz) and runs a 1 MiB streaming bench in both 1-lane (fast read
    0x0B) and quad-output (0x6B) modes at each step, reporting elapsed
    ms, KB/s, CRC32, and first-error offset against the expected
    incrementing pattern (i & 0xFF over the whole address space).
2026-04-28 baremetal/qspi: retune PLL4 for 166 MHz QSPI; bench diag improvements
    PLL4 is reconfigured in src/setup.c::sysclk_init from M=2/N=50/P=12
    (VCO 612 MHz, P=47 MHz) to M=3/N=82/P=1 (VCO 664 MHz, P=332 MHz).
    perclk_init now routes the QSPI kernel clock to PLL4P. At
    prescaler=1, SCLK lands exactly at 166 MHz, the DS13483 Table 76
    SDR Fmax_QSPI at VDD>=2.7 V with CL<=20 pF. PLL4-derived ETH and
    SDMMC kernel clocks shift off their nominal values; this demo
2026-04-28 baremetal/{uart_echo,qspi}: bring up DDR+MMU; expand auto tests
    uart_echo: trim further to a no-op CLI shell (just `reset` and a new
    1 MB PRBS write/readback DDR self-test); restore ddr_init+mmu_init.
    README/verify.py exercise prompt, echo, unknown-command, and the DDR
    self-test via run_md.py.
    qspi: enable HAL_DDR/MDMA/DMA modules and add ddr.c so future bench
    work can MDMA QSPI -> DDR without hitting the SRAM ceiling. Default
2026-04-28 baremetal/qspi: expose raw (no-opcode/no-addr) mode for plain SPI slaves
    QUADSPI's CCR forces an opcode (and optionally an address) byte onto
    the wire ahead of the data phase. Plain SPI slaves don't speak flash
    framing -- those prepended bytes shift their MISO pattern and break
    byte-accurate tests.
    Add an explicit raw mode:
    - bench: third arg `raw=0/1` skips IMODE / ADMODE in the CCR.
2026-04-28 baremetal/qspi: README: program qspi.bin onto FPGA in Block 1
    Makes the suite order-independent w.r.t. other FPGA test suites that
    leave a different bitstream loaded (e.g. the upstream spi chapter
    that programs spi_1lane.bin / spi_quad.bin). Subsequent blocks rely
    on FPGA-state persistence across bench_mcu:reset_dut within one
    run_md.py invocation, so only Block 1 needs the explicit reprogram.
    The qspi.bin blob lives in the FPGA-side repo; run_md.py looks it up
2026-04-28 baremetal/qspi: README: program qspi.bin in every block, not only Block 1
    test_serv serializes per-device, not per-suite, so a concurrent
    run_md.py invocation can slot its own fpga:program between our
    blocks. Block 1 alone is therefore not enough to guarantee that
    the FPGA is running qspi.bin when the rest of the suite executes.
2026-04-28 baremetal/qspi: drive Block 12 at datasheet-max SCLK (166 MHz)
    Tighten the MDMA streaming block: presc=3 (~166 MHz wire SCLK, the
    STM32MP135 datasheet maximum per DS13483 Rev 5 page 170, Table 76),
    not the previous presc=15 fast-but-conservative setting. Bullet
    threshold raised from 50 Mbps to 200 Mbps to match -- empirical run
    sustains ~261 Mbps quad into DDR over 16 MB. presc=2 (~221 MHz) is
    over-spec and the FPGA stub stops responding there, so 261 Mbps is
2026-04-28 baremetal/qspi: Block 12 throughput bullet cites 664 Mbps datasheet-max bit rate
2026-04-29 Update QSPI MDMA bring-up support
2026-04-29 qspi: add sustained stream crc path
2026-05-01 qspi: add stream observability controls
2026-05-01 Update EVB boot image and SSH overlay
    Build the EVB path with DTS=stm32mp135f-dk and CFLAGS_EXTRA=-DEVB
    instead of editing the custom-board DTS.
    Keep bench SSH public keys in the usual overlay location while removing
    tracked key material from Git and ignoring regenerated overlay keys.
2026-05-03 qspi: I command for mmap_spi bit-integrity probe (work-in-progress)
    Adds the I <bytes> CLI command (cmd_mmap_int + mdma_mm_to_dst
    helper extension with src_offset parameter) implementing twin-DDR
    ping-pong validation over QSPI memory-mapped MDMA reads.
    Status: throughput cleared at 655 Mbps wall-rate over 1024 chunks
    (>400 Mbps mission gate met) but bit-integrity validation reveals
    the qspi.bin slave is not suitable for mmap-mode address-
2026-05-05 qspi: invalidate dest after MM-MDMA + force unconditional ABORT in mm_disable
    Two fixes for the 4-lane memory-mapped + MDMA path so subsequent
    transfers see deterministic data and don't wedge the channel:
    - mdma_mm_to_dst (cli.c): post-MDMA L1 D-cache InvalidateMVA over
    the destination range, mirroring qspi_mdma_finish in the indirect
    path. Cortex-A7 speculative prefetch can pull stale DDR lines into
    cache before MDMA writes land; pre-clean alone leaves a window where
2026-05-05 qspi mm-MDMA: drop SBURST from 16-beat to single beat
    QSPI's memory-mapped AHB slave (FMODE=11) does not cleanly service
    16-beat AHB read bursts: with SBURST=4 the channel transferred exactly
    one 64 B buffer (BNDT=0xFFC0) on the first MDMA call after each
    qspi_mm_disable / qspi_mm_enable then stalled with CRQA stuck at 1,
    and the readback on the very first 16-beat burst showed a deterministic
    single-bit toggle mid-burst (a8980848 vs a8180848 at word 1, byte 2).
2026-05-05 Bump bootloader to flash.tsv blob-name fix
    Pulls in 0bb0ec1 which drops the `build/` path prefix on
    `scripts/flash.tsv`'s Binary column, so test_serv's dfu plugin
    accepts the blob reference (it rejects filesystem paths).
2026-05-05 Bump bootloader pointer to rewritten history (Co-Author trailers stripped)
2026-05-05 Add GPIO connectivity dry run
2026-05-05 Generate GPIO connectivity command scripts
2026-05-05 Add GPIO connectivity test vectors
2026-05-05 Record bootloader for SSH custom mission
2026-05-05 Add custom NAND image configuration
2026-05-05 Add GPIO connectivity replay fixtures
2026-05-05 Add GPIO replay contract validator
2026-05-06 Update bootloader for faster NAND MSC
2026-05-06 Add MP135 GPIO NCS drive output
2026-05-06 Add MP135 GPIO SCLK drive output
2026-05-06 Add MP135 GPIO IO1 sample output
2026-05-06 Add MP135 GPIO SCLK UART trigger
2026-05-06 Report MP135 IO1 samples periodically
2026-05-06 Add MP135 gpio_test image
2026-05-06 Add MP135 GPIO IO1 high UART trigger
2026-05-06 Add MP135 GPIO SCLK low UART trigger
2026-05-06 Add MP135 GPIO IO3 high UART trigger
2026-05-06 Add MP135 GPIO IO2 sample output
2026-05-06 Size NAND rootfs for stress writes
2026-05-06 Build NAND rootfs with UBIFS free-space fixup
2026-05-06 Stabilize NAND boot image provisioning
2026-05-06 gpio_test: add IO1 low UART trigger 'r' command
2026-05-06 gpio_test: add IO3 low UART trigger 'b' command
2026-05-06 baremetal: add prbs_test skeleton with LFSR
2026-05-07 gpio_test: commit reset_n on iCEstick pin 112
    Replace the TBD FPGA-side pin in the reset_n jumper with the
    already-bound pins[0] / iCEstick pin 112 from gpio.nw's PCF.
2026-05-07 gpio_test: commit ctrl_start on iCEstick 113
    Replace the TBD FPGA pin in the ctrl_start jumper row with
    iCEstick pin 113, reusing the pins[1] slot already bound in
    gpio.nw's PCF chunk.
2026-05-07 gpio_test: TODO control-GPIO MPU pins still TBD
    Document in gpio_replay_mpu_stub.c that reset_n, ctrl_start, and
    status_output replay vectors silently no-op until MP135 GPIO ports
    are selected and the per-signal tables are extended.
2026-05-07 Audit MPU QSPI replay manifest coverage
2026-05-07 Add prbs_test UART ready banner
2026-05-07 Add prbs_test UART reset command
2026-05-07 Trace unused clock shutdown
2026-05-07 Enable EVB configfs USB gadget base
2026-05-08 Add USBTMC MSC backing file init script
2026-05-08 Add EVB MSC gadget descriptor init script
2026-05-08 Port custom DTS to ST 6.6 SDMMC boot
2026-05-08 Trace after unused-clock skip
2026-05-08 Trace post-bkpsram next clock
2026-05-08 Keep STM32MP135 SSH target on static IP
2026-05-08 Make SSH root key install reliable
2026-05-08 Record upstream kernel refresh target
2026-05-08 Add MP135 PRBS checksum print command
2026-05-09 usbtmc: enable MSC configfs gadget
2026-05-09 usbtmc: link mass_storage function into c.1 config
2026-05-09 usbtmc: bind MSC gadget to UDC at boot
2026-05-09 patch.linux: keep eth1tx enabled in unused
2026-05-09 patch.linux: add post-eth1tx next-clock latch
2026-05-09 Makefile: add sd-unix target
    Pack a unix-flavoured SD image: bootloader main.stm32 at the LBA-128
    unpartitioned slot, then unix-v7-c99/unix and unix-v7-c99/root.img
    as MBR partitions for the bench bootloader's two+jump flow. The V7
    kernel needs no DTB so the layout is shorter than the Linux sd: target.
2026-05-09 Makefile: sd-unix lays kernel at LBA 896
    Bench bootloader's `two` command default reads the kernel from SD
    block 896 and the dtb from 640. Stack a 0-byte placeholder file
    into the 640 slot so sdimage.py's preferred-LBA logic places the
    unix kernel at 896, matching the bootloader expectation.
2026-05-10 Restore custom clock driver and add static IPs
    The v6.6-stm32mp upgrade dropped a ~700-line custom-clock-driver patch
    that the local single-stage bootloader path depends on. Without it the
    kernel cannot program PLL3, CK_AXI, PCLK*, RTCAPB, etc. directly and the
    stmmac PHY init times out. Bring those clocks back into
    stm32mp13_clock_cfg[] with SECF_NONE so the kernel programs the RCC
    itself (no SCMI / no PSCI / no OP-TEE / no TF-A).
2026-05-10 sd-unix: kernel as MBR partition 0, not LBA-896
    The bootloader's `two` handler is sd_load_mbr(), which reads the MBR
    table and copies partition[0] to DEF_LINUX_ADDR (0xC2000000) and
    partition[1] to DEF_DTB_ADDR. The prior layout put the unix ELF at
    positional LBA 896 (ignored by sd_load_mbr) and root.img as MBR
    partition 0, so `two` loaded the rootfs to 0xC2000000 and `jump`
    executed root.img bytes as code.
2026-05-13 make it work on linux 6.1 again
2026-05-13 hardcode the MAC address
2026-05-19 NAND boot hardening
    - bigger kernel MTD slot (4-203, 50 MB) so PT/DTB mirror blocks 202/203
    sit inside it instead of inside the UBIFS rootfs where wear-leveling
    would erase them; rootfs starts at block 204.
    - nandflipbits in the rootfs so the BCH fault-injection test can flip
    bits on a live mtd partition.
    - kernel patch adds one dev_warn so a corrected BCH bit-flip shows up in
2026-05-21 random agentic mess
2026-05-24 remove junk files
2026-05-26 upgrade to v6.6
2026-05-27 add websockets test streamer
2026-05-27 speedup sd card msc
2026-05-28 Use upstream stable Linux submodule
2026-05-28 wip getting usbtmc to work
2026-05-29 use shared prbs algo
2026-06-11 use buildroot to build kernel
2026-06-25 claude does something with the internet

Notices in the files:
baremetal/uart_echo/src/board.h:
@copyright 2026 Jakob Kastelic
config/custom.dts:
SPDX-License-Identifier: (GPL-2.0+ OR BSD-3-Clause)
Copyright (C) STMicroelectronics 2021 - All Rights Reserved
